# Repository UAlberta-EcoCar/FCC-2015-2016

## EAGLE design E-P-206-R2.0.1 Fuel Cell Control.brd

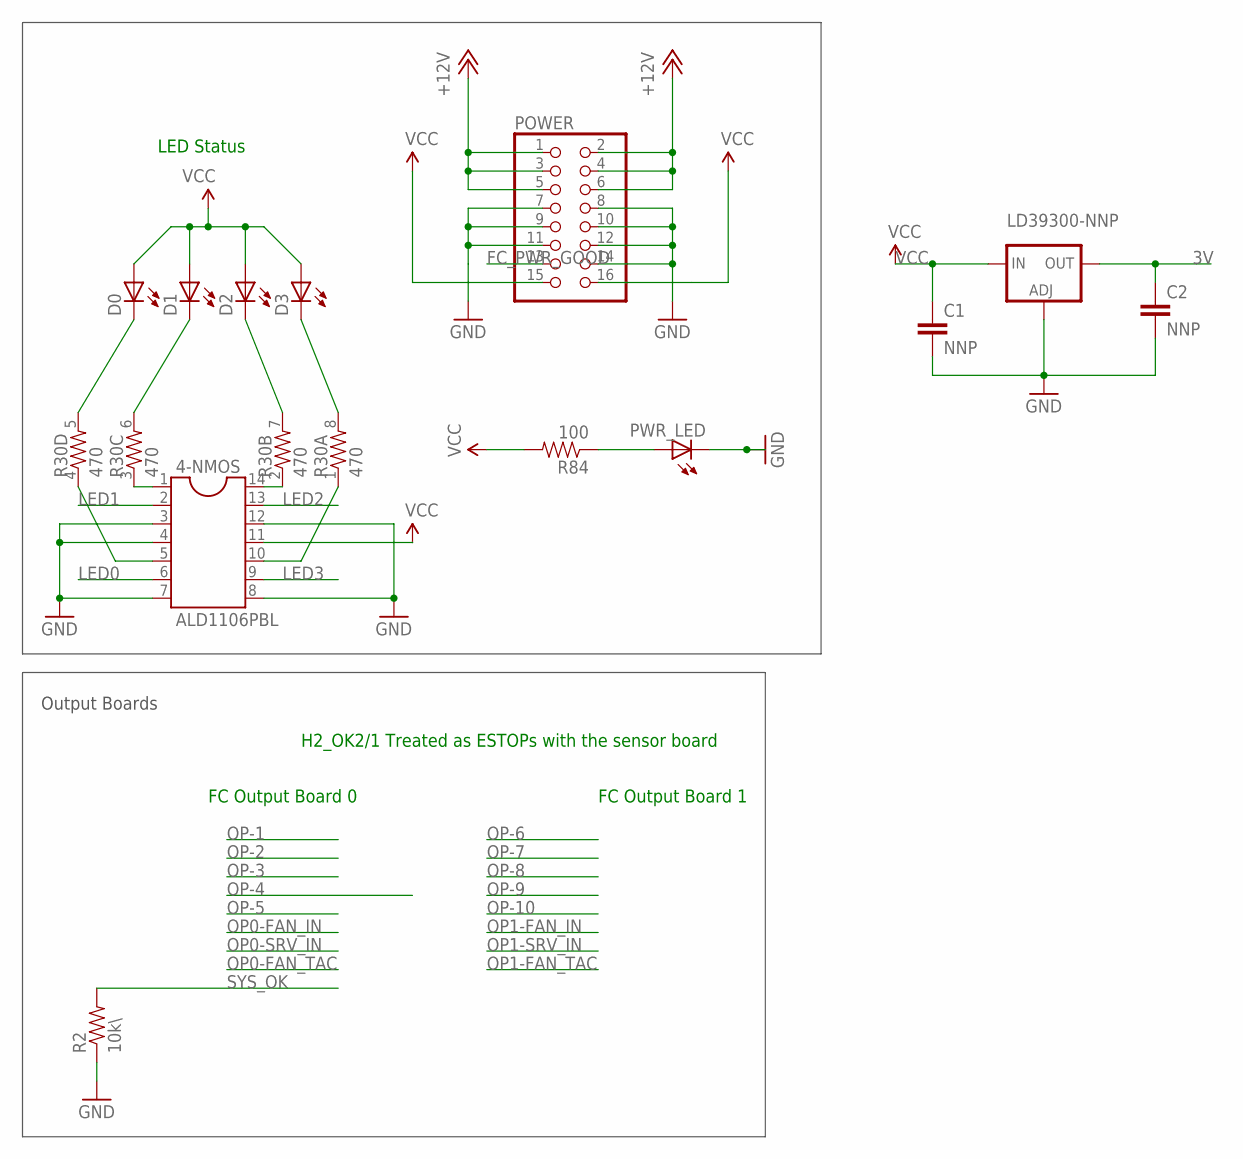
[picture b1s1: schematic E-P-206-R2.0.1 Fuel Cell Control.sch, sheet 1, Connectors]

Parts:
4-NMOS: ALD1106PBL; SOIC-14
C1, C2: NNP; 1206
D0, D1, D2, D3: LED1206; LED-1206
LD39300-NNP: LD117ADT50TR; DPACK
POWER: PINHD-2X8; 2X08
PWR_LED: LED1206; LED-1206
R2: 10k\; 0603-RES
R30: 470; 0603-ARV
R84: 100; 0603-RES

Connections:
3V: C2.1, LD39300-NNP.4 (OUT); also elsewhere on the board
+12V: POWER.1, POWER.2, POWER.3, POWER.4, POWER.5, POWER.6; also elsewhere on the board
FC_PWR_GOOD: POWER.13
GND: 4-NMOS.3, 4-NMOS.4, 4-NMOS.7, 4-NMOS.8, 4-NMOS.12, C1.2, C2.2, LD39300-NNP.1 (ADJ), POWER.7, POWER.8, POWER.9, POWER.10, POWER.11, POWER.12, POWER.14, PWR_LED.C, R2.1; also elsewhere on the board
LED0: 4-NMOS.6; also elsewhere on the board
LED0_O: D0.C, R30.5 (2)
LED1: 4-NMOS.2; also elsewhere on the board
LED1_O: D1.C, R30.6 (2)
LED2: 4-NMOS.13; also elsewhere on the board
LED2_O: D2.C, R30.7 (2)
LED3: 4-NMOS.9; also elsewhere on the board
LED3_O: D3.C, R30.8 (2)
unnamed: 4-NMOS.5, R30.4 (1)
unnamed: 4-NMOS.1, R30.3 (1)
unnamed: 4-NMOS.14, R30.2 (1)
unnamed: 4-NMOS.10, R30.1
unnamed: PWR_LED.A, R84.1
SYS_OK: R2.2; also elsewhere on the board
VCC: 4-NMOS.11, C1.1, D0.A, D1.A, D2.A, D3.A, LD39300-NNP.3 (IN), POWER.15, POWER.16, R84.2; also elsewhere on the board

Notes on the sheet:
FC Output Board 0
Output Boards
FC Output Board 1
LED Status
H2_OK2/1 Treated as ESTOPs with the sensor board

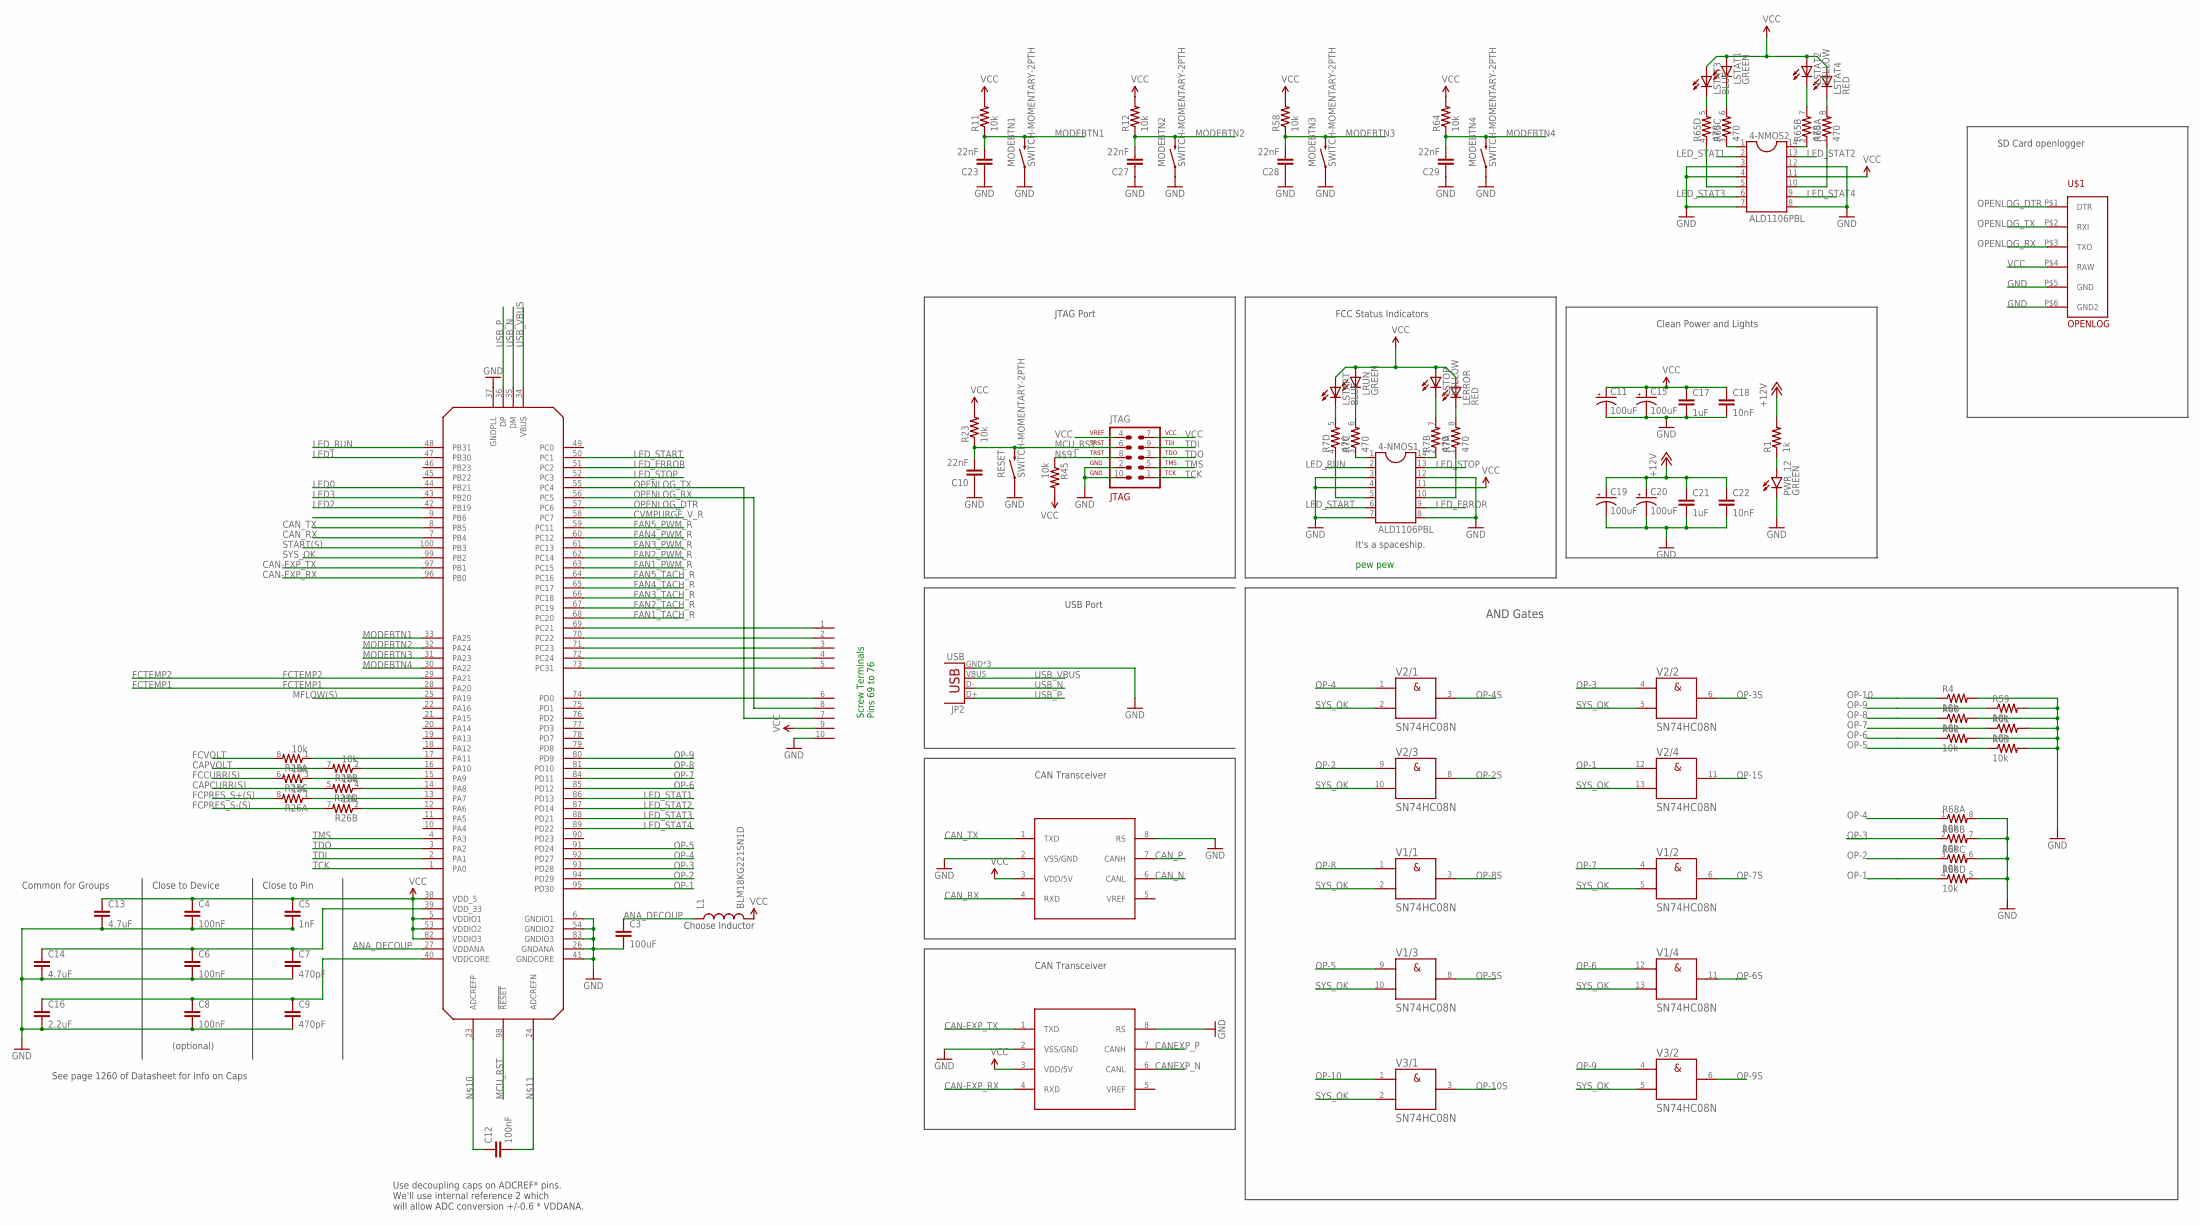
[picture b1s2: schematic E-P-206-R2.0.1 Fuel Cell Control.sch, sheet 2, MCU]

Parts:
4-NMOS1, 4-NMOS2: ALD1106PBL; SOIC-14
C3: 100uF; 0805
C4, C6, C8: 100nF; 0603-CAP
C5: 1nF; 0603-CAP
C7, C9: 470pF; 0603-CAP
C10, C23, C27, C28, C29: 22nF; 0603-CAP
C11, C15, C19, C20: 100uF; PANASONIC_C
C12: 100nF; 0805
C13, C14: 4.7uF; 0805
C16: 2.2uF; 0805
C17, C21: 1uF; 0805
C18, C22: 10nF; 0603-CAP
JP2: USB; USB-MICROB
JTAG: 2x5; AVR-JTAG-10
L1: BLM18KG221SN1D; 0603
LERROR: RED; LED-1206
LRUN: GREEN; LED-1206
LSTART: BLUE; LED-1206
LSTAT1: GREEN; LED-1206
LSTAT2: YELLOW; LED-1206
LSTAT3: BLUE; LED-1206
LSTAT4: RED; LED-1206
LSTOP: YELLOW; LED-1206
MCU: AT32UC3C1512; TQFP100
MODEBTN1, MODEBTN2, MODEBTN3, MODEBTN4: SWITCH-MOMENTARY-2PTH; TACTILE-PTH
PWR_12: GREEN; LED-1206
R1: 1k; 0603-RES
R4, R11, R12, R23, R45, R58, R59, R60, R61, R62, R63, R64: 10k; 0603-RES
R7, R65: 470; 0603-ARV
R25, R26, R68: 10k; 0603-ARV
RESET: SWITCH-MOMENTARY-2PTH; TACTILE-PTH
SCREWTERMINAL: 10X1PCBBLOCK
U$1: OPENLOG
U$4, U$36: MCP2551; 8-SOIC
V1, V2, V3: SN74HC08N; DIL14

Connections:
+12V: C19.+, C20.+, C21.1, C22.1, R1.2; also elsewhere on the board
+UB: V1.14 (+UB), V2.14 (+UB), V3.14 (+UB)
-UB: V1.7 (-UB), V2.7 (-UB), V3.7 (-UB)
ANA_DECOUP: C3.1, L1.1, MCU.27 (VDDANA)
CAN-EXP_RX: MCU.96 (PB0), U$36.4 (RXD)
CAN-EXP_TX: MCU.97 (PB1), U$36.1 (TXD)
CANEXP_N: U$36.6 (CANL)
CANEXP_P: U$36.7 (CANH)
CAN_N: U$4.6 (CANL)
CAN_P: U$4.7 (CANH)
CAN_RX: MCU.7 (PB4), U$4.4 (RXD)
CAN_TX: MCU.8 (PB5), U$4.1 (TXD)
CAPCURR(S): R25.5 (2); also elsewhere on the board
CAPVOLT: R25.7 (2); also elsewhere on the board
CVMPURGE_V_R: MCU.58 (PC7); also elsewhere on the board
FAN1_PWM_R: MCU.63 (PC15); also elsewhere on the board
FAN1_TACH_R: MCU.68 (PC20); also elsewhere on the board
FAN2_PWM_R: MCU.62 (PC14); also elsewhere on the board
FAN2_TACH_R: MCU.67 (PC19); also elsewhere on the board
FAN3_PWM_R: MCU.61 (PC13); also elsewhere on the board
FAN3_TACH_R: MCU.66 (PC18); also elsewhere on the board
FAN4_PWM_R: MCU.60 (PC12); also elsewhere on the board
FAN4_TACH_R: MCU.65 (PC17); also elsewhere on the board
FAN5_PWM_R: MCU.59 (PC11); also elsewhere on the board
FAN5_TACH_R: MCU.64 (PC16); also elsewhere on the board
FCCURR(S): R25.6 (2); also elsewhere on the board
FCPRES_S+(S): R26.8 (2); also elsewhere on the board
FCPRES_S-(S): R26.7 (2); also elsewhere on the board
FCTEMP1: MCU.28 (PA20); also elsewhere on the board
FCTEMP2: MCU.29 (PA21); also elsewhere on the board
FCVOLT: R25.8 (2); also elsewhere on the board
GND: 4-NMOS1.3, 4-NMOS1.4, 4-NMOS1.7, 4-NMOS1.8, 4-NMOS1.12, 4-NMOS2.8, 4-NMOS2.12, C3.2, C4.2, C5.2, C6.2, C7.2, C8.2, C9.2, C10.1, C11.-, C13.2, C14.2, C15.-, C16.2, C17.2, C18.2, C19.-, C20.-, C21.2, C22.2, C23.1, C27.1, C28.1, C29.1, JP2.GND, JP2.MT1 (GND), JP2.MT2 (GND), JTAG.2, JTAG.10, MCU.6 (GNDIO1), MCU.26 (GNDANA), MCU.37 (GNDPLL), MCU.41 (GNDCORE), MCU.54 (GNDIO2), MCU.83 (GNDIO3), MODEBTN1.1, MODEBTN2.1, MODEBTN3.1, MODEBTN4.1, PWR_12.C, R4.2, R59.2, R60.2, R61.2, R62.2, R63.2, R68.5 (2), R68.6 (2), R68.7 (2), R68.8 (2), RESET.1, SCREWTERMINAL.10, U$1.P$5 (GND), U$1.P$6 (GND2), U$4.2 (VSS/GND), U$4.8 (RS), U$36.2 (VSS/GND), U$36.8 (RS); also elsewhere on the board
LED0: MCU.44 (PB21); also elsewhere on the board
LED1: MCU.47 (PB30); also elsewhere on the board
LED2: MCU.42 (PB19); also elsewhere on the board
LED3: MCU.43 (PB20); also elsewhere on the board
LED_ERROR: 4-NMOS1.9, MCU.51 (PC2)
LED_RUN: 4-NMOS1.2, MCU.48 (PB31)
LED_START: 4-NMOS1.6, MCU.50 (PC1)
LED_STAT1: 4-NMOS2.2, MCU.86 (PD13)
LED_STAT2: 4-NMOS2.13, MCU.87 (PD14)
LED_STAT3: 4-NMOS2.3, 4-NMOS2.4, 4-NMOS2.6, 4-NMOS2.7, MCU.88 (PD21)
LED_STAT4: 4-NMOS2.9, MCU.89 (PD22)
LED_STOP: 4-NMOS1.13, MCU.52 (PC3)
MCU_RST: C10.2, JTAG.6, MCU.98 (!RESET), R23.1, RESET.3 (2); also elsewhere on the board
MFLOW(S): MCU.25 (PA19); also elsewhere on the board
MODEBTN1: C23.2, MCU.33 (PA25), MODEBTN1.3 (2), R11.1
MODEBTN2: C27.2, MCU.32 (PA24), MODEBTN2.3 (2), R12.1
MODEBTN3: C28.2, MCU.31 (PA23), MODEBTN3.3 (2), R58.1
MODEBTN4: C29.2, MCU.30 (PA22), MODEBTN4.3 (2), R64.1
unnamed: MCU.12 (PA6), R26.2 (1)
unnamed: MCU.13 (PA7), R26.1
unnamed: C6.1, C7.1, C14.1, MCU.39 (VDD_33)
unnamed: C8.1, C9.1, C16.1, MCU.40 (VDDCORE)
unnamed: C12.1, MCU.23 (ADCREFP)
unnamed: C12.2, MCU.24 (ADCREFN)
unnamed: MCU.14 (PA8), R25.4 (1)
unnamed: LSTART.C, R7.5 (2)
unnamed: LRUN.C, R7.6 (2)
unnamed: MCU.15 (PA9), R25.3 (1)
unnamed: MCU.16 (PA10), R25.2 (1)
unnamed: MCU.17 (PA11), R25.1
unnamed: 4-NMOS1.5, R7.4 (1)
unnamed: 4-NMOS1.1, R7.3 (1)
unnamed: PWR_12.A, R1.1
unnamed: 4-NMOS2.5, R65.4 (1)
unnamed: 4-NMOS2.1, R65.3 (1)
unnamed: 4-NMOS2.14, R65.2 (1)
unnamed: 4-NMOS2.10, R65.1
unnamed: LSTAT3.C, R65.5 (2)
unnamed: 4-NMOS1.14, R7.2 (1)
unnamed: 4-NMOS1.10, R7.1
unnamed: LSTOP.C, R7.7 (2)
unnamed: LERROR.C, R7.8 (2)
unnamed: LSTAT1.C, R65.6 (2)
unnamed: LSTAT2.C, R65.7 (2)
unnamed: LSTAT4.C, R65.8 (2)
unnamed: JTAG.8, R45.1
OP-1: MCU.95 (PD30), R68.4 (1), V2.12 (A)
OP-1S: V2.11 (Y); also elsewhere on the board
OP-2: MCU.94 (PD29), R68.3 (1), V2.9 (A)
OP-2S: V2.8 (Y); also elsewhere on the board
OP-3: MCU.93 (PD28), R68.2 (1), V2.4 (A)
OP-3S: V2.6 (Y); also elsewhere on the board
OP-4: MCU.92 (PD27), R68.1, V2.1 (A)
OP-4S: V2.3 (Y); also elsewhere on the board
OP-5: MCU.91 (PD24), R63.1, V1.9 (A)
OP-5S: V1.8 (Y); also elsewhere on the board
OP-6: MCU.85 (PD12), R62.1, V1.12 (A)
OP-6S: V1.11 (Y); also elsewhere on the board
OP-7: MCU.84 (PD11), R61.1, V1.4 (A)
OP-7S: V1.6 (Y); also elsewhere on the board
OP-8: MCU.81 (PD10), R60.1, V1.1 (A)
OP-8S: V1.3 (Y); also elsewhere on the board
OP-9: MCU.80 (PD9), R59.1, V3.4 (A)
OP-9S: V3.6 (Y); also elsewhere on the board
OP-10: R4.1, V3.1 (A)
OP-10S: V3.3 (Y); also elsewhere on the board
OPENLOG_DTR: MCU.57 (PC6), U$1.P$1 (DTR)
OPENLOG_RX: MCU.56 (PC5), SCREWTERMINAL.8, U$1.P$3 (TXO)
OPENLOG_TX: MCU.55 (PC4), SCREWTERMINAL.7, U$1.P$2 (RXI)
PC21: MCU.69 (PC21), SCREWTERMINAL.1
PC22: MCU.70 (PC22), SCREWTERMINAL.2
PC23: MCU.71 (PC23), SCREWTERMINAL.3
PC24: MCU.72 (PC24), SCREWTERMINAL.4
PC31: MCU.73 (PC31), SCREWTERMINAL.5
PD0: MCU.74 (PD0), SCREWTERMINAL.6
START(S): MCU.100 (PB3); also elsewhere on the board
SYS_OK: MCU.99 (PB2), V1.2 (B), V1.5 (B), V1.10 (B), V1.13 (B), V2.2 (B), V2.5 (B), V2.10 (B), V2.13 (B), V3.2 (B), V3.5 (B); also elsewhere on the board
TCK: JTAG.1, MCU.1 (PA0)
TDI: JTAG.9, MCU.2 (PA1)
TDO: JTAG.3, MCU.3 (PA2)
TMS: JTAG.5, MCU.4 (PA3)
USB_N: JP2.D-, MCU.35 (DM)
USB_P: JP2.D+, MCU.36 (DP)
USB_VBUS: JP2.VBUS, MCU.34 (VBUS)
VCC: 4-NMOS1.11, 4-NMOS2.11, C4.1, C5.1, C11.+, C13.1, C15.+, C17.1, C18.1, JTAG.4, JTAG.7, L1.2, LERROR.A, LRUN.A, LSTART.A, LSTAT1.A, LSTAT2.A, LSTAT3.A, LSTAT4.A, LSTOP.A, MCU.5 (VDDIO1), MCU.38 (VDD_5), MCU.53 (VDDIO2), MCU.82 (VDDIO3), R11.2, R12.2, R23.2, R45.2, R58.2, R64.2, SCREWTERMINAL.9, U$1.P$4 (RAW), U$4.3 (VDD/5V), U$36.3 (VDD/5V); also elsewhere on the board

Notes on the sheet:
Choose Inductor
Use decoupling caps on ADCREF* pins. We'll use internal reference 2 which will allow ADC conversion +/-0.6 * VDDANA.
Close to Pin
Close to Device
Common for Groups
JTAG Port
USB Port
(optional)
See page 1260 of Datasheet for info on Caps
CAN Transceiver
Clean Power and Lights
FCC Status Indicators
It's a spaceship.
pew pew
AND Gates
Screw Terminals Pins 69 to 76
SD Card openlogger

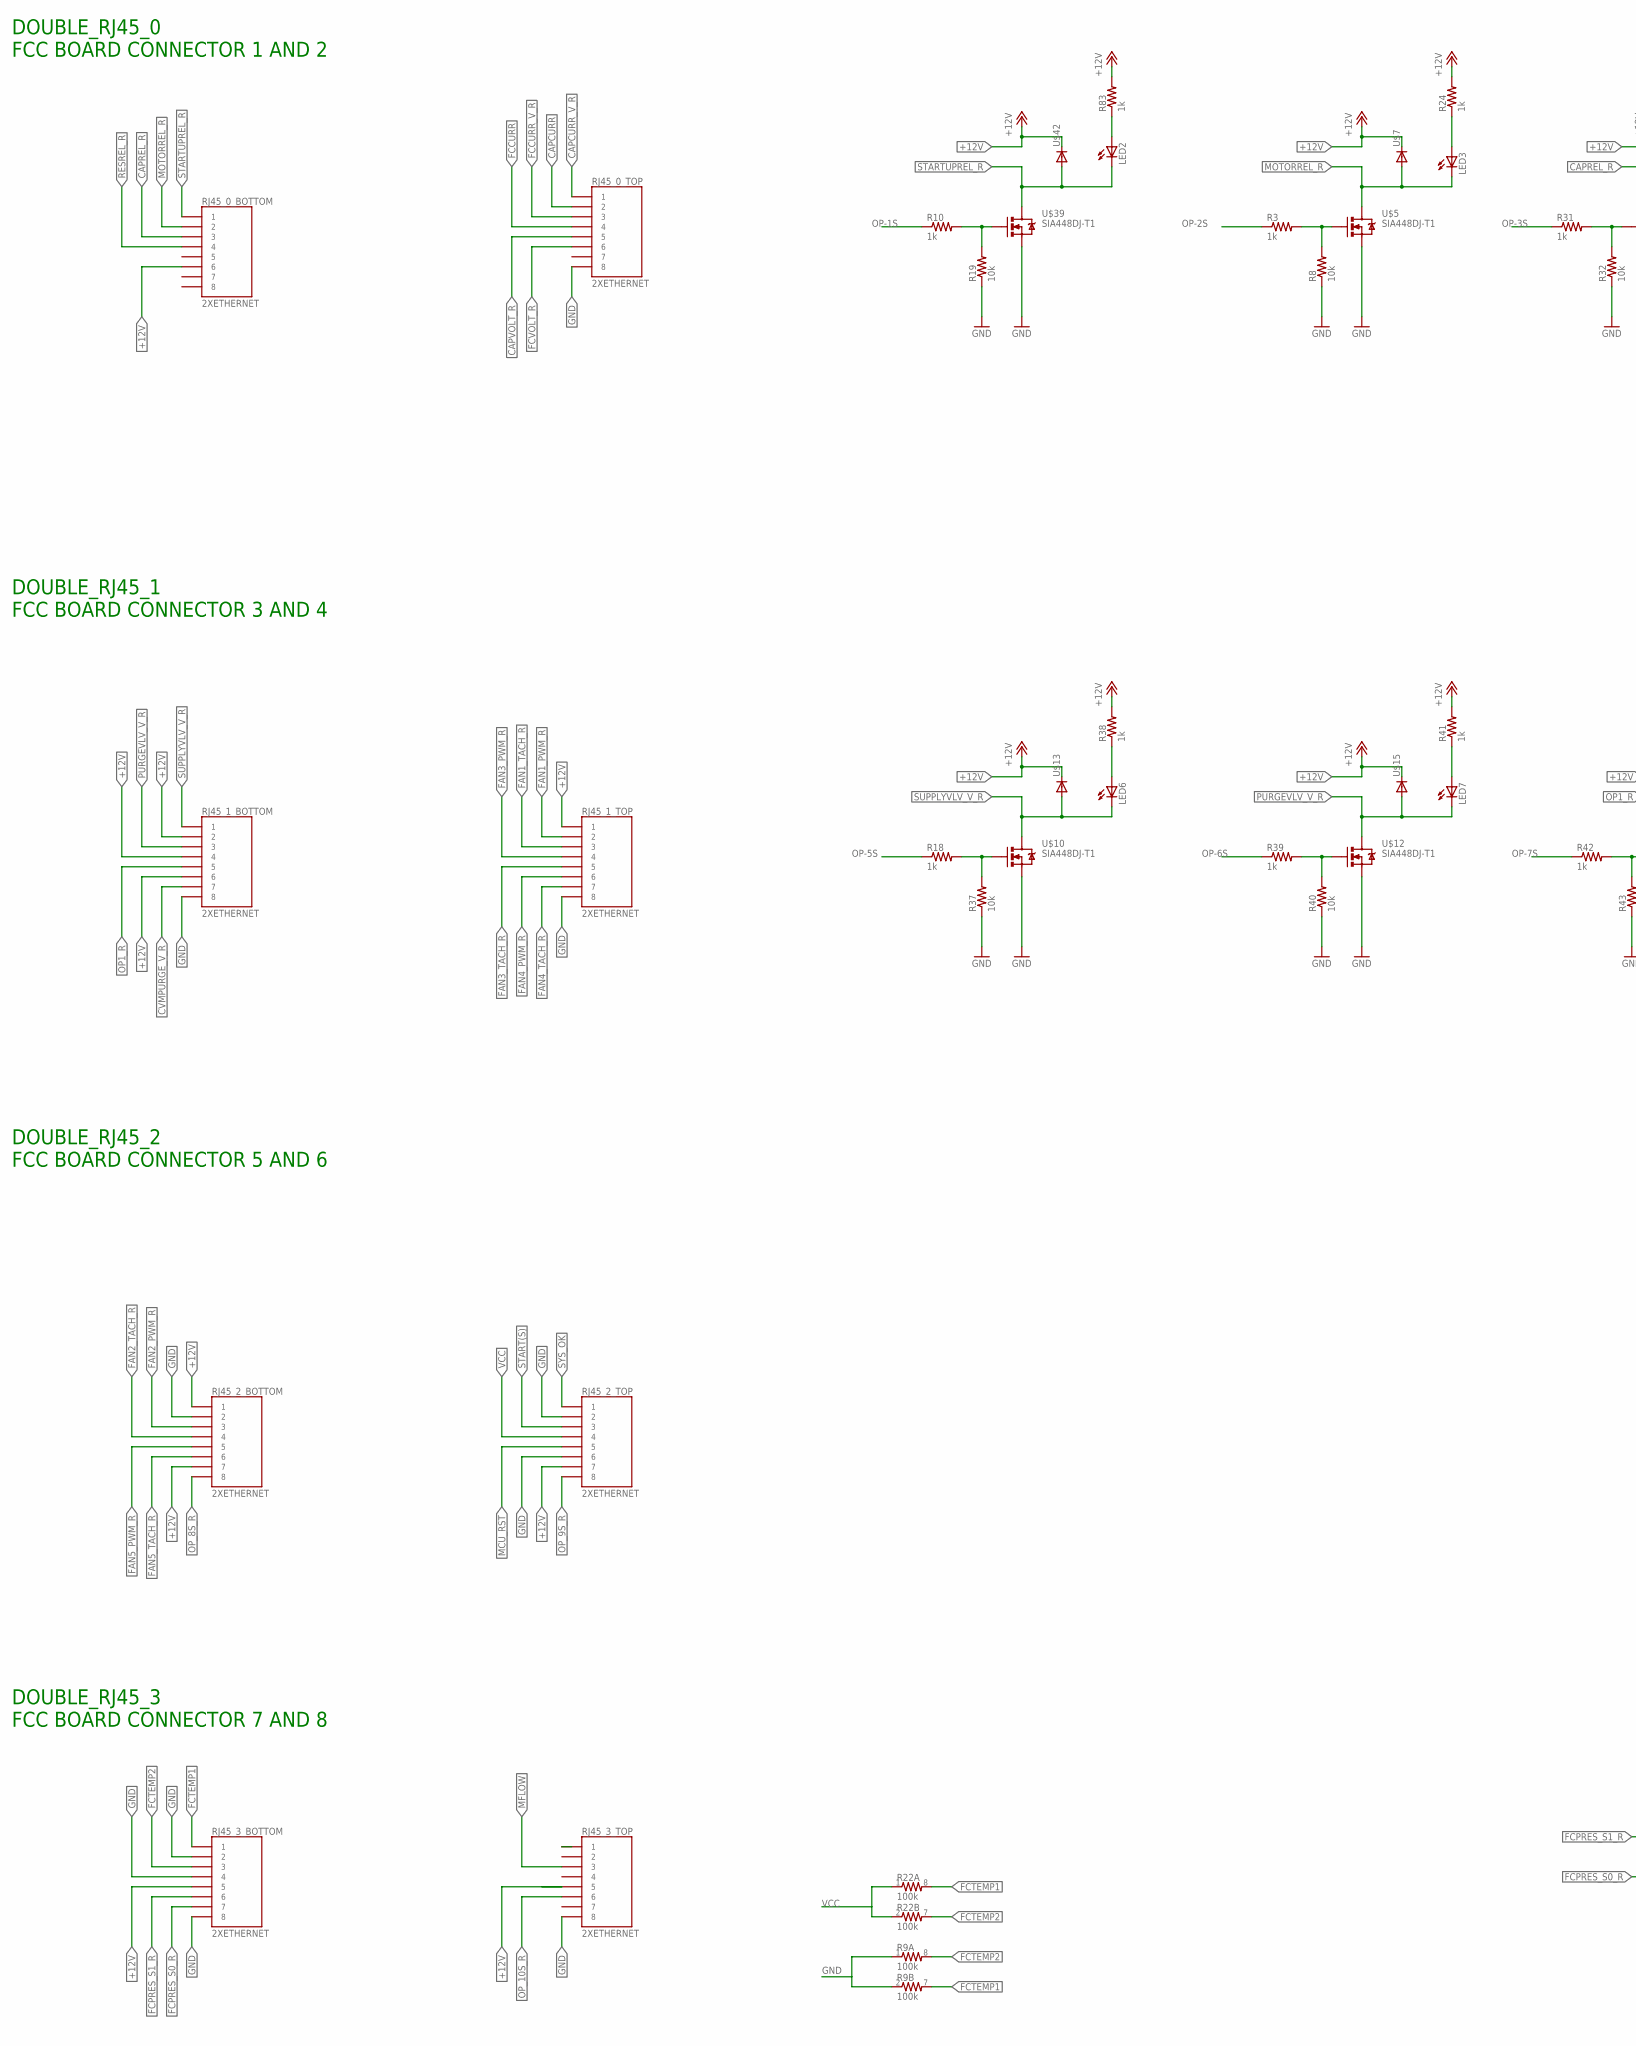
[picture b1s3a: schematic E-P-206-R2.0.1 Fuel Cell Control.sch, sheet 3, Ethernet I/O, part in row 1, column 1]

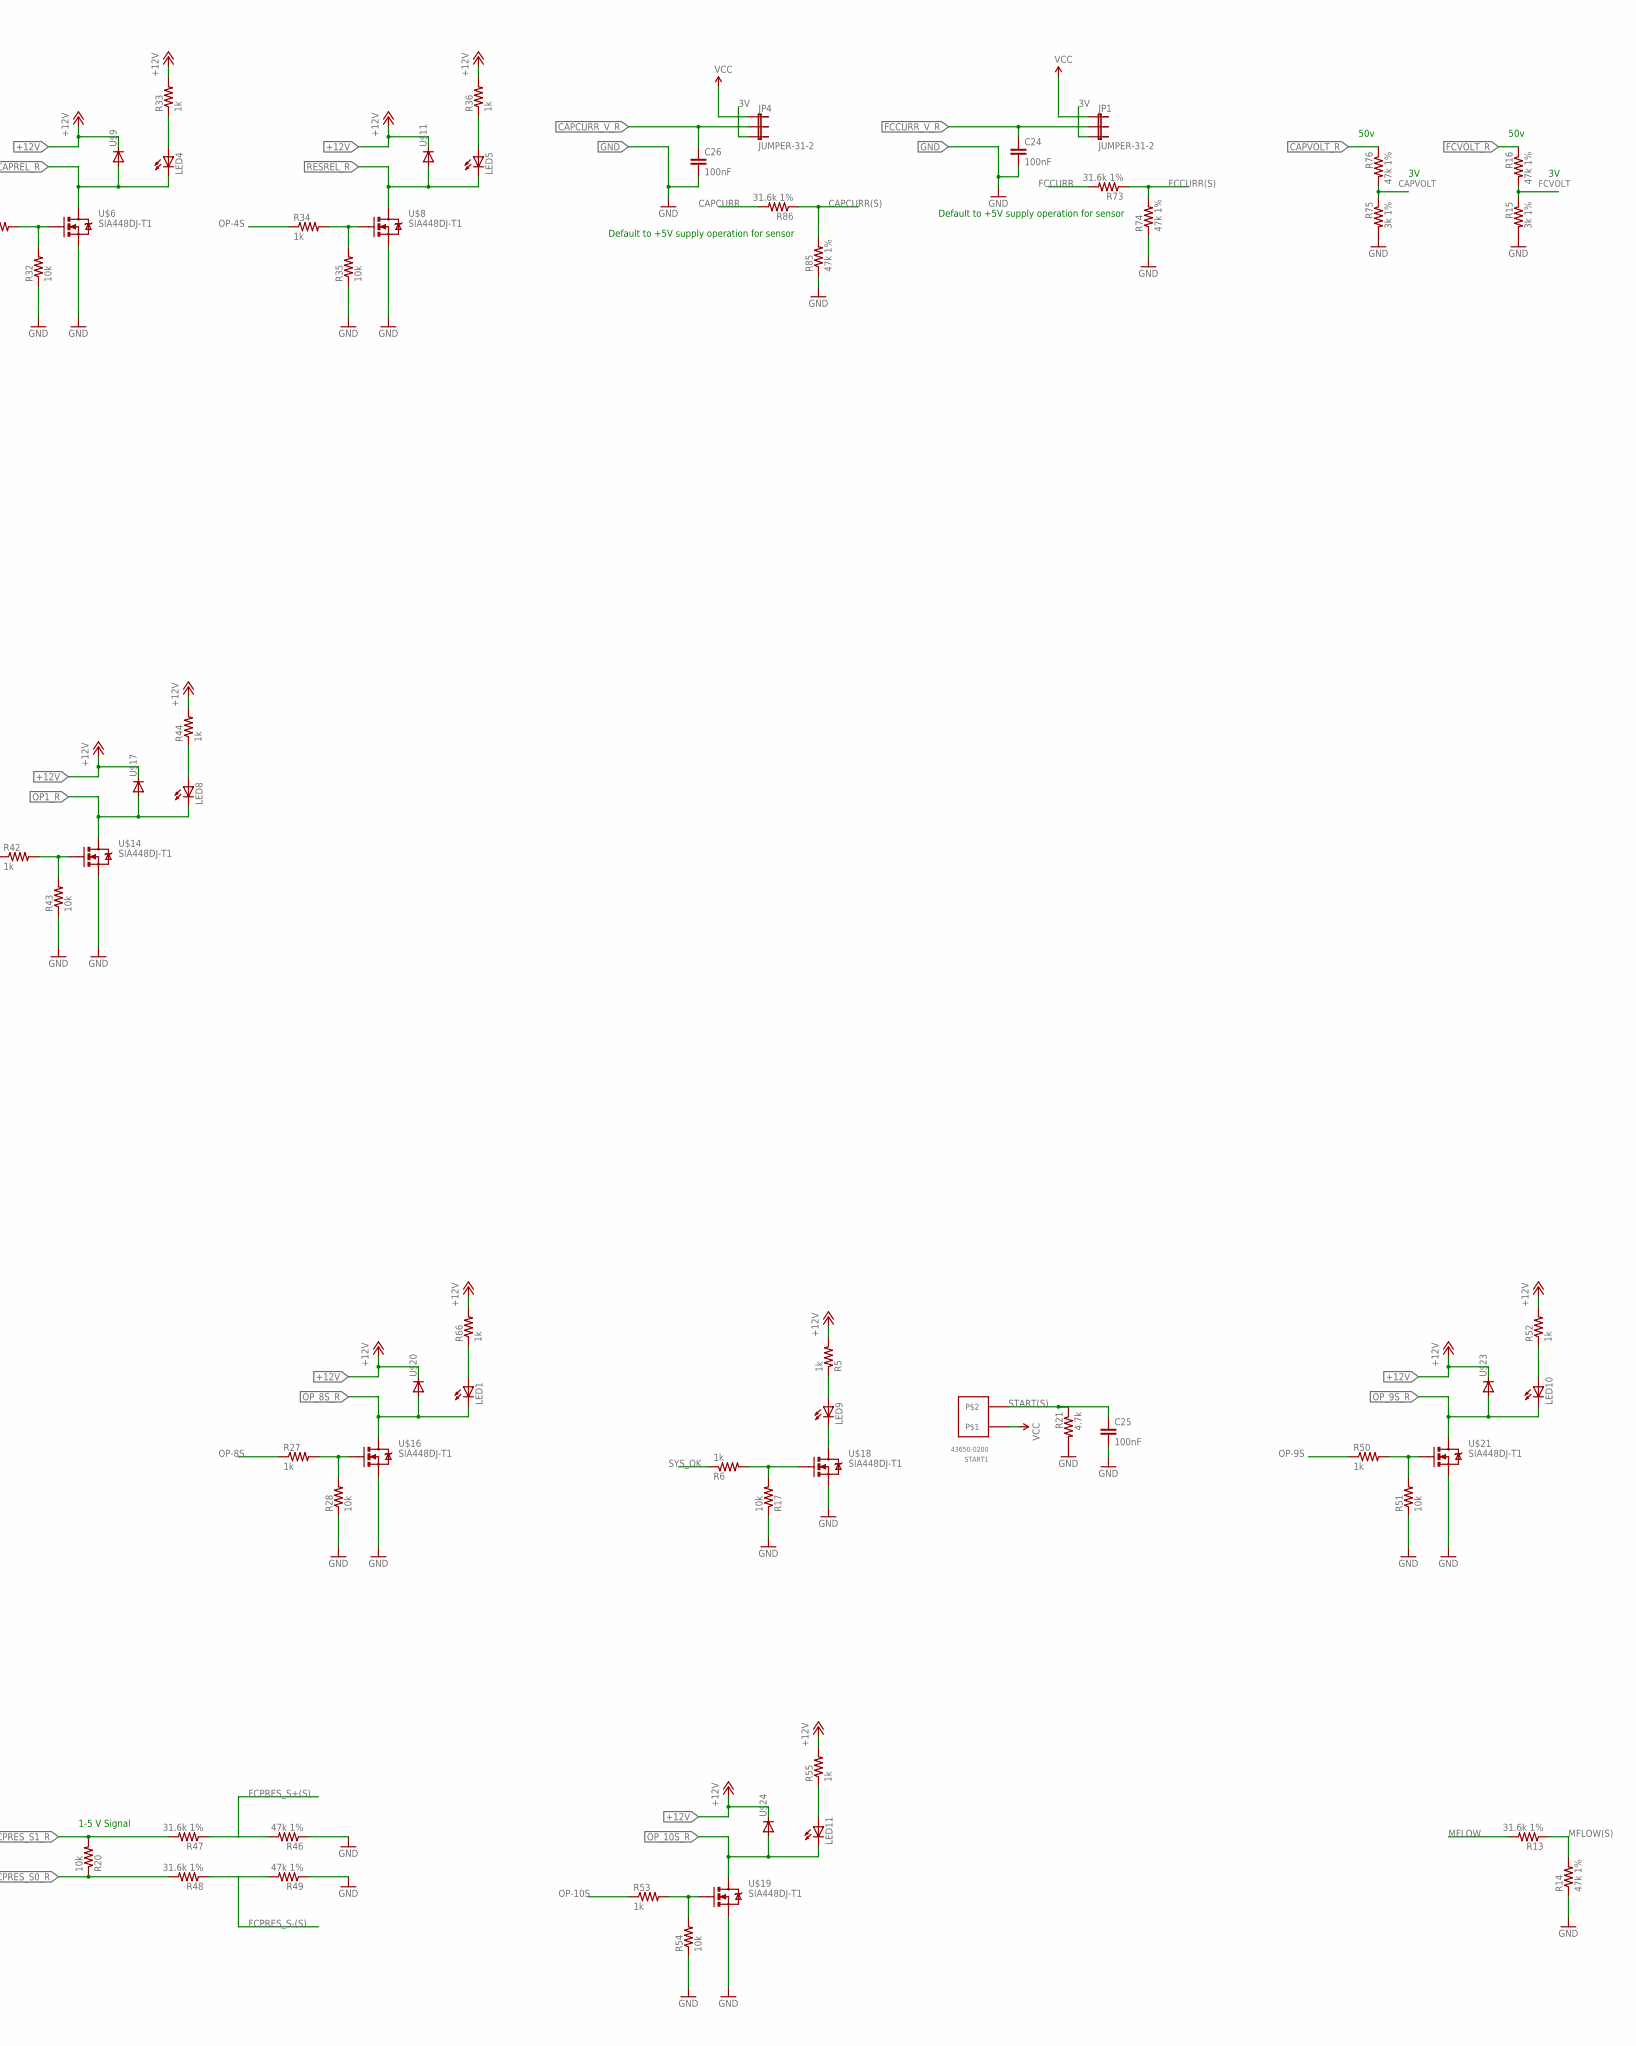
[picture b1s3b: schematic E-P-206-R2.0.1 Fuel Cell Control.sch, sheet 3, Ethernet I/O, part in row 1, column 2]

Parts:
C24, C25, C26: 100nF; 0603-CAP
JP1, JP4: JUMPER-31-2; SJ_3_PASTE1&2
LED1, LED2, LED3, LED4, LED5, LED6, LED7, LED8, LED9, LED10, LED11: LED1206; LED-1206
R3, R5, R6, R10, R18, R24, R27, R31, R33, R34, R36, R38, R39, R41, R42, R44, R50, R52, R53, R55, R66, R83: 1k; 0603-RES
R8, R17, R19, R20, R28, R32, R35, R37, R40, R43, R51, R54: 10k; 0603-RES
R9, R22: 100k; 0603-ARV
R13, R47, R48, R73, R86: 31.6k 1%; 0603-RES
R14, R16, R46, R49, R74, R76, R85: 47k 1%; 0603-RES
R15, R75: 3k 1%; 0603-RES
R21: 4.7k; 0603-RES
RJ45_0_, RJ45_1_, RJ45_2_, RJ45_3_: 2XETHERNET
START1: 43650-0200
U$5, U$6, U$8, U$10, U$12, U$14, U$16, U$18, U$19, U$21, U$39: SIA448DJ-T1; SC70-6L
U$7, U$9, U$11, U$13, U$15, U$17, U$20, U$23, U$24, U$42: DIODE-DO214AC; DO214AC

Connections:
3V: JP1.3, JP4.3; also elsewhere on the board
+12V: R5.2, R24.2, R33.2, R36.2, R38.2, R41.2, R44.2, R52.2, R55.2, R66.2, R83.2, RJ45_0_.B_6 (6), RJ45_1_.B_2 (2), RJ45_1_.B_4 (4), RJ45_1_.B_6 (6), RJ45_1_.T_1 (1), RJ45_2_.B_1 (1), RJ45_2_.B_7 (7), RJ45_2_.T_7 (7), RJ45_3_.B_5 (5), RJ45_3_.T_5 (5), U$7.C, U$9.C, U$11.C, U$13.C, U$15.C, U$17.C, U$20.C, U$23.C, U$24.C, U$42.C; also elsewhere on the board
CAPCURR: R86.2, RJ45_0_.T_2 (2)
CAPCURR(S): R85.2, R86.1; also elsewhere on the board
CAPCURR_V_R: C26.1, JP4.2, RJ45_0_.T_1 (1)
CAPREL_R: LED4.C, RJ45_0_.B_3 (3), U$6.D, U$9.A
CAPVOLT: R75.1, R76.2; also elsewhere on the board
CAPVOLT_R: R76.1, RJ45_0_.T_5 (5)
CVMPURGE_V_R: RJ45_1_.B_7 (7); also elsewhere on the board
FAN1_PWM_R: RJ45_1_.T_2 (2); also elsewhere on the board
FAN1_TACH_R: RJ45_1_.T_3 (3); also elsewhere on the board
FAN2_PWM_R: RJ45_2_.B_3 (3); also elsewhere on the board
FAN2_TACH_R: RJ45_2_.B_4 (4); also elsewhere on the board
FAN3_PWM_R: RJ45_1_.T_4 (4); also elsewhere on the board
FAN3_TACH_R: RJ45_1_.T_5 (5); also elsewhere on the board
FAN4_PWM_R: RJ45_1_.T_6 (6); also elsewhere on the board
FAN4_TACH_R: RJ45_1_.T_7 (7); also elsewhere on the board
FAN5_PWM_R: RJ45_2_.B_5 (5); also elsewhere on the board
FAN5_TACH_R: RJ45_2_.B_6 (6); also elsewhere on the board
FCCURR: R73.2, RJ45_0_.T_4 (4)
FCCURR(S): R73.1, R74.2; also elsewhere on the board
FCCURR_V_R: C24.1, JP1.2, RJ45_0_.T_3 (3)
FCPRES_S0_R: R20.1, R48.2, RJ45_3_.B_7 (7)
FCPRES_S1_R: R20.2, R47.2, RJ45_3_.B_6 (6)
FCPRES_S+(S): R46.2, R47.1; also elsewhere on the board
FCPRES_S-(S): R48.1, R49.2; also elsewhere on the board
FCTEMP1: R9.7 (2), R22.8 (2), RJ45_3_.B_1 (1); also elsewhere on the board
FCTEMP2: R9.8 (2), R22.7 (2), RJ45_3_.B_3 (3); also elsewhere on the board
FCVOLT: R15.1, R16.2; also elsewhere on the board
FCVOLT_R: R16.1, RJ45_0_.T_6 (6)
GND: C24.2, C25.2, C26.2, R8.1, R9.1, R9.2 (1), R14.1, R15.2, R17.1, R19.1, R21.2, R28.1, R32.1, R35.1, R37.1, R40.1, R43.1, R46.1, R49.1, R51.1, R54.1, R74.1, R75.2, R85.1, RJ45_0_.T_8 (8), RJ45_1_.B_8 (8), RJ45_1_.T_8 (8), RJ45_2_.B_2 (2), RJ45_2_.T_2 (2), RJ45_2_.T_6 (6), RJ45_3_.B_2 (2), RJ45_3_.B_4 (4), RJ45_3_.B_8 (8), RJ45_3_.T_1 (1), RJ45_3_.T_8 (8), U$5.S@0 (S), U$5.S@1 (S), U$6.S@0 (S), U$6.S@1 (S), U$8.S@0 (S), U$8.S@1 (S), U$10.S@0 (S), U$10.S@1 (S), U$12.S@0 (S), U$12.S@1 (S), U$14.S@0 (S), U$14.S@1 (S), U$16.S@0 (S), U$16.S@1 (S), U$18.S@0 (S), U$18.S@1 (S), U$19.S@0 (S), U$19.S@1 (S), U$21.S@0 (S), U$21.S@1 (S), U$39.S@0 (S), U$39.S@1 (S); also elsewhere on the board
MCU_RST: RJ45_2_.T_5 (5); also elsewhere on the board
MFLOW: R13.2, RJ45_3_.T_3 (3)
MFLOW(S): R13.1, R14.2; also elsewhere on the board
MOTORREL_R: LED3.C, RJ45_0_.B_2 (2), U$5.D, U$7.A
unnamed: LED9.A, R5.1
unnamed: R10.2, R19.2, U$39.G
unnamed: LED9.C, U$18.D
unnamed: R3.2, R8.2, U$5.G
unnamed: LED2.A, R83.1
unnamed: R31.2, R32.2, U$6.G
unnamed: LED3.A, R24.1
unnamed: R34.2, R35.2, U$8.G
unnamed: LED4.A, R33.1
unnamed: R18.2, R37.2, U$10.G
unnamed: LED5.A, R36.1
unnamed: R27.2, R28.2, U$16.G
unnamed: R39.2, R40.2, U$12.G
unnamed: LED6.A, R38.1
unnamed: R42.2, R43.2, U$14.G
unnamed: LED7.A, R41.1
unnamed: R50.2, R51.2, U$21.G
unnamed: LED8.A, R44.1
unnamed: R53.2, R54.2, U$19.G
unnamed: R6.2, R17.2, U$18.G
unnamed: LED1.A, R66.1
unnamed: LED10.A, R52.1
unnamed: LED11.A, R55.1
OP1_R: LED8.C, RJ45_1_.B_5 (5), U$14.D, U$17.A
OP-1S: R10.1; also elsewhere on the board
OP-2S: R3.1; also elsewhere on the board
OP-3S: R31.1; also elsewhere on the board
OP-4S: R34.1; also elsewhere on the board
OP-5S: R18.1; also elsewhere on the board
OP-6S: R39.1; also elsewhere on the board
OP-7S: R42.1; also elsewhere on the board
OP-8S: R27.1; also elsewhere on the board
OP-9S: R50.1; also elsewhere on the board
OP-10S: R53.1; also elsewhere on the board
OP_8S_R: LED1.C, RJ45_2_.B_8 (8), U$16.D, U$20.A
OP_9S_R: LED10.C, RJ45_2_.T_8 (8), U$21.D, U$23.A
OP_10S_R: LED11.C, RJ45_3_.T_6 (6), U$19.D, U$24.A
PURGEVLV_V_R: LED7.C, RJ45_1_.B_3 (3), U$12.D, U$15.A
RESREL_R: LED5.C, RJ45_0_.B_4 (4), U$8.D, U$11.A
START(S): C25.1, R21.1, RJ45_2_.T_3 (3), START1.P$1; also elsewhere on the board
STARTUPREL_R: LED2.C, RJ45_0_.B_1 (1), U$39.D, U$42.A
SUPPLYVLV_V_R: LED6.C, RJ45_1_.B_1 (1), U$10.D, U$13.A
SYS_OK: R6.1, RJ45_2_.T_1 (1); also elsewhere on the board
VCC: JP1.1, JP4.1, R22.1, R22.2 (1), RJ45_2_.T_4 (4), START1.P$2; also elsewhere on the board

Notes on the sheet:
DOUBLE_RJ45_0 FCC BOARD CONNECTOR 1 AND 2
DOUBLE_RJ45_1 FCC BOARD CONNECTOR 3 AND 4
DOUBLE_RJ45_2 FCC BOARD CONNECTOR 5 AND 6
DOUBLE_RJ45_3 FCC BOARD CONNECTOR 7 AND 8
Default to +5V supply operation for sensor
50v
1-5 V Signal

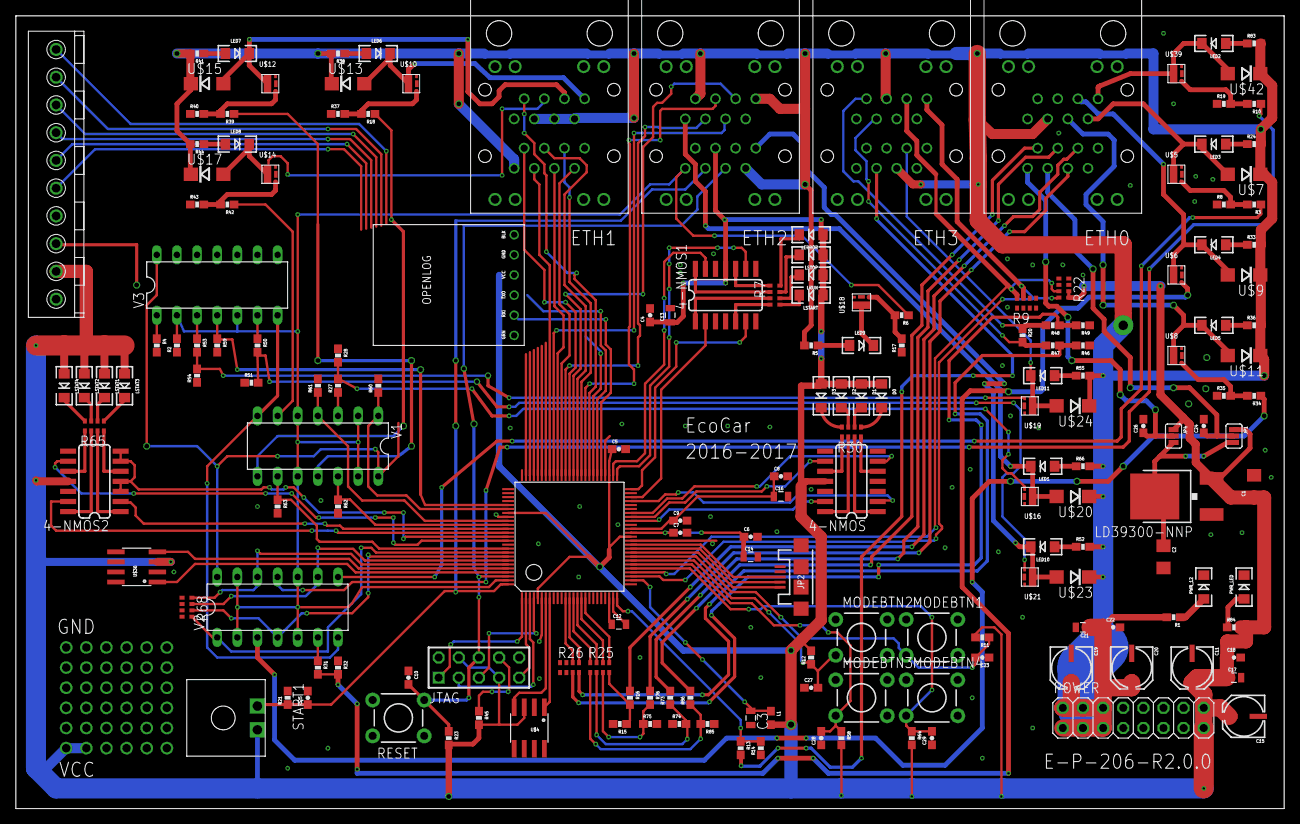
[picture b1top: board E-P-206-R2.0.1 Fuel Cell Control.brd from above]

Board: 2 copper layers, 160.0 x 100.0 mm, 175 parts (0 on the bottom side), 165 nets.

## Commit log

2017-01-10 this is the first update
2017-01-10 Reverting to Andy's copy
2017-01-10 Just some renaming of the files
2017-01-11 Added some silkscreening and updated the relay board connection
2017-01-11 Second update
2017-01-11 Ready to gerber
2017-02-11 Some random housekeeping items

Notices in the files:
parts and their libraries:
SparkFun: Licensing: CC v3.0 Share-Alike You are welcome to use this library for commercial purposes.
SparkFun-Capacitors: Licensing: Creative Commons ShareAlike 4.0 International - https://creativecommons.org/licenses/by-sa/4.0
